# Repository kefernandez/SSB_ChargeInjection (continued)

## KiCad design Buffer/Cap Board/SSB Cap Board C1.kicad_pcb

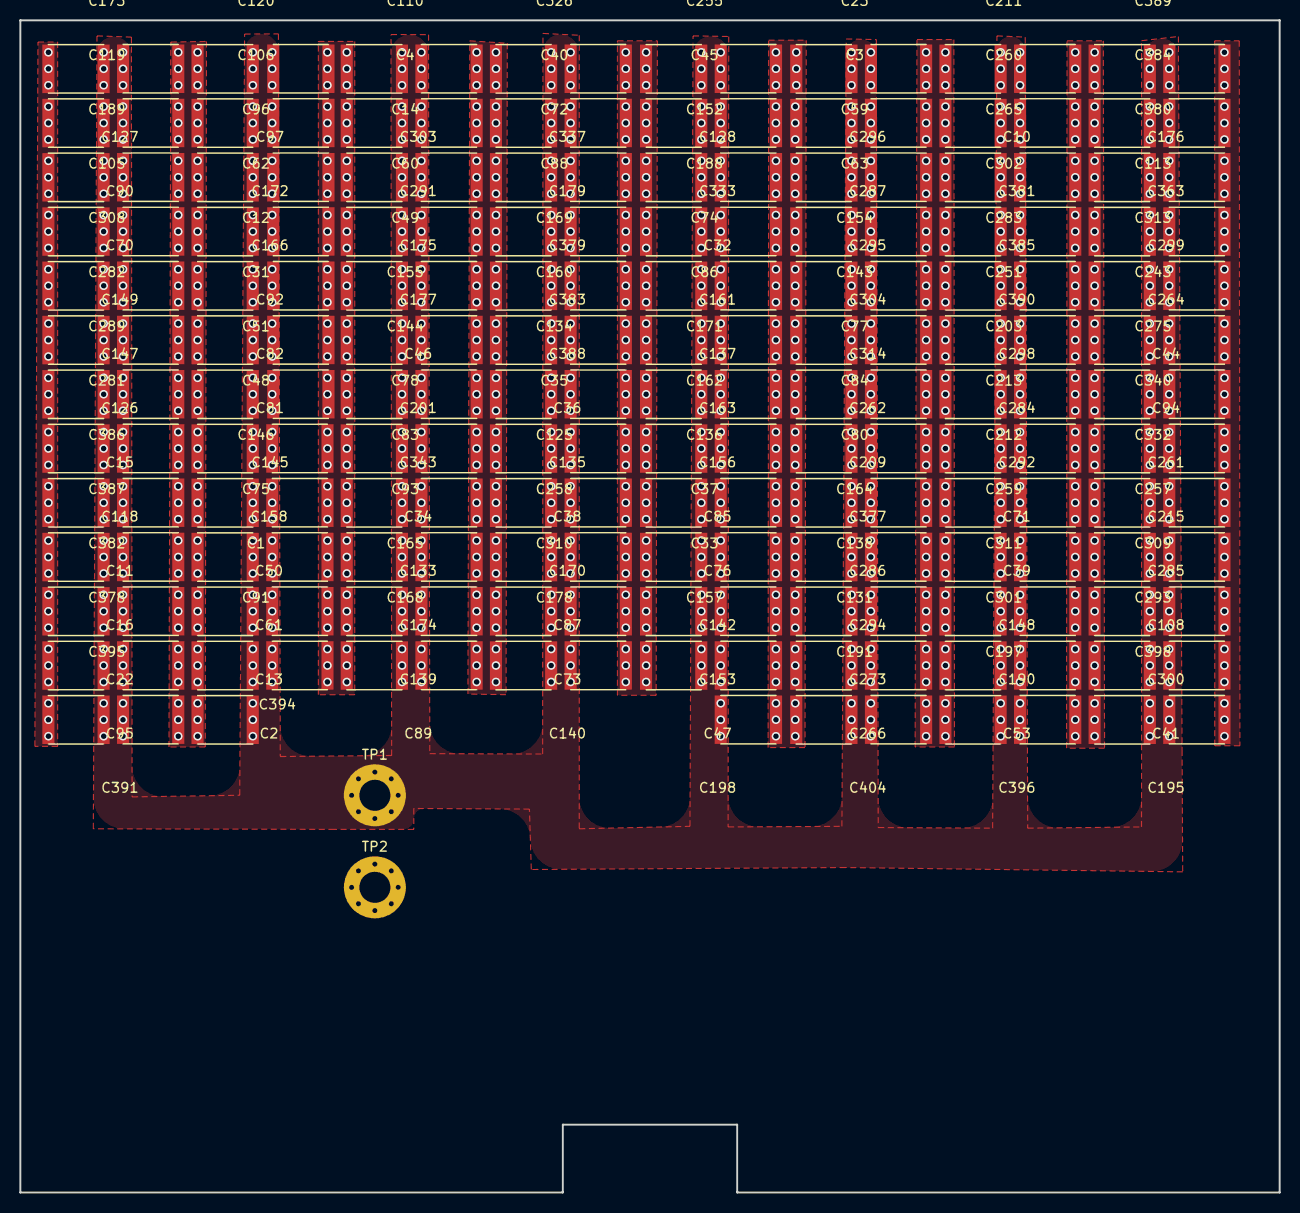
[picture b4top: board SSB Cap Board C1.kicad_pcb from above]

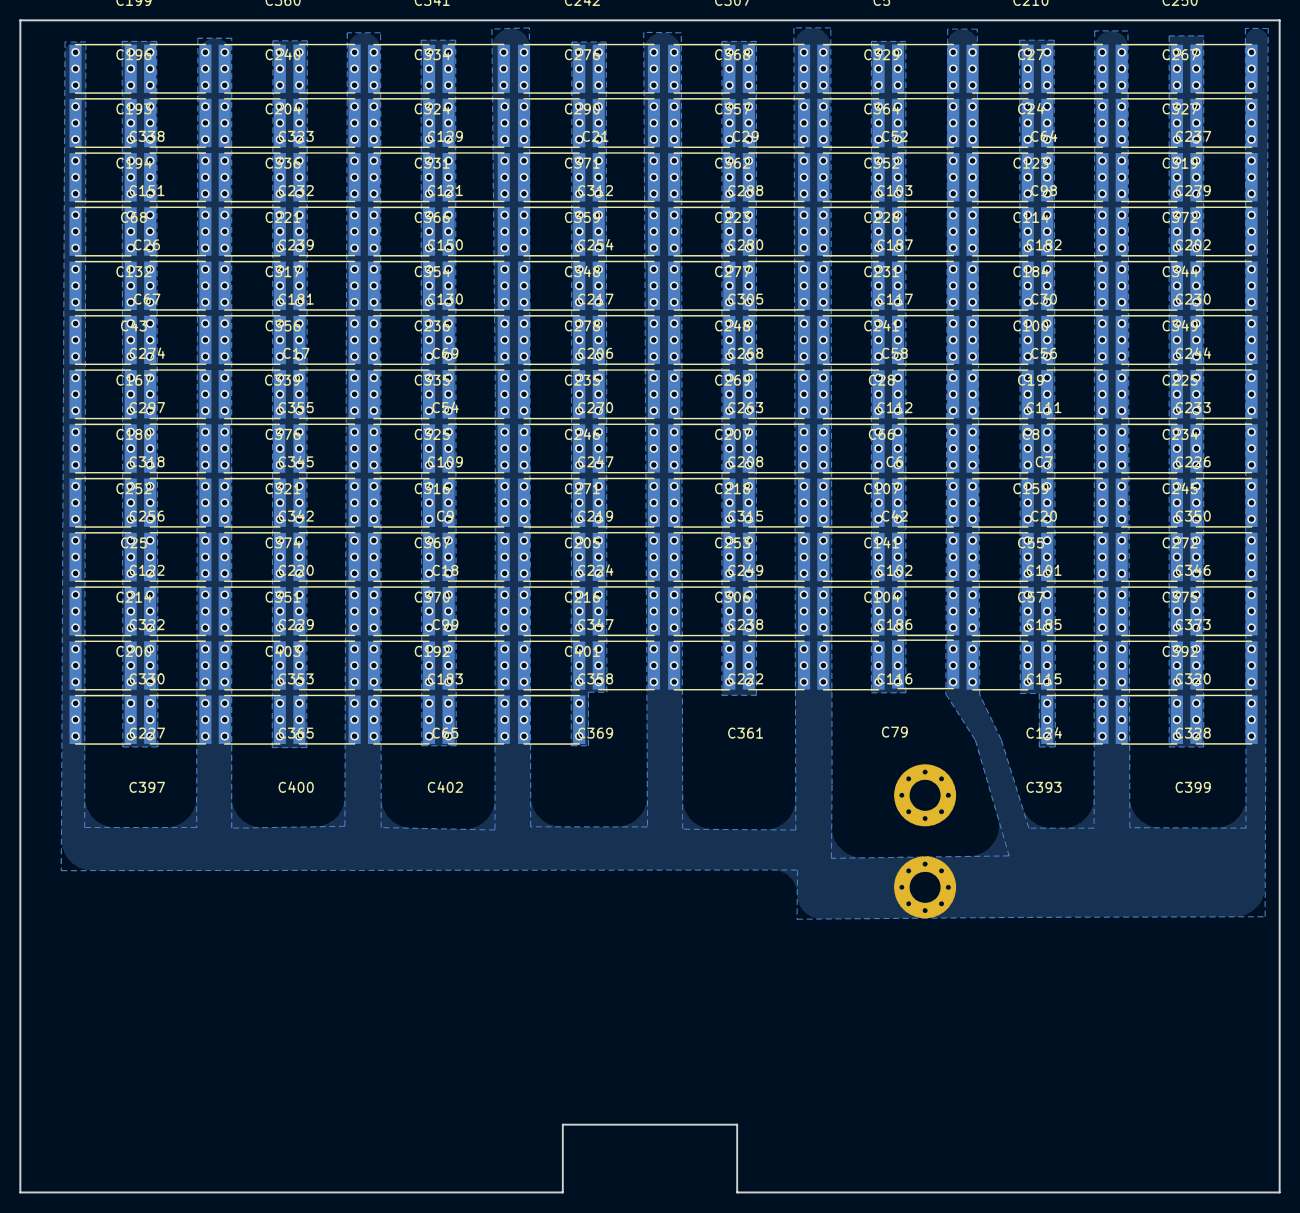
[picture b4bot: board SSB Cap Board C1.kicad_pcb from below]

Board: 2 copper layers, 130.0 x 121.0 mm, 406 parts (202 on the bottom side), 2 nets, no tracks yet.

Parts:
C1, C2, C3, C4, C5, C6, C7, C8, C9, C10, C11, C12, C13, C14, C15, C16, C17, C18, C19, C20, C21, C22, C23, C24, C25, C26, C27, C28, C29, C30, C31, C32, C33, C34, C35, C36, C37, C38, C39, C40, C41, C42, C43, C44, C45, C46, C47, C48, C49, C50, C51, C52, C53, C54, C55, C56, C57, C58, C59, C60, C61, C62, C63, C64, C65, C66, C67, C68, C69, C70, C71, C72, C73, C74, C75, C76, C77, C78, C79, C80, C81, C82, C83, C84, C85, C86, C87, C88, C89, C90, C91, C92, C93, C94, C95, C96, C97, C98, C99, C100, C101, C102, C103, C104, C105, C106, C107, C108, C109, C110, C111, C112, C113, C114, C115, C116, C117, C118, C119, C120, C121, C122, C123, C124, C125, C126, C127, C128, C129, C130, C131, C132, C133, C134, C135, C136, C137, C138, C139, C140, C141, C142, C143, C144, C145, C146, C147, C148, C149, C150, C151, C152, C153, C154, C155, C156, C157, C158, C159, C160, C161, C162, C163, C164, C165, C166, C167, C168, C169, C170, C171, C172, C173, C174, C175, C176, C177, C178, C179, C180, C181, C182, C183, C184, C185, C186, C187, C188, C189, C190, C191, C192, C193, C194, C195, C196, C197, C198, C199, C200, C201, C202, C203, C204, C205, C206, C207, C208, C209, C210, C211, C212, C213, C214, C215, C216, C217, C218, C219, C220, C221, C222, C223, C224, C225, C226, C227, C228, C229, C230, C231, C232, C233, C234, C235, C236, C237, C238, C239, C240, C241, C242, C243, C244, C245, C246, C247, C248, C249, C250, C251, C252, C253, C254, C255, C256, C257, C258, C259, C260, C261, C262, C263, C264, C265, C266, C267, C268, C269, C270, C271, C272, C273, C274, C275, C276, C277, C278, C279, C280, C281, C282, C283, C284, C285, C286, C287, C288, C289, C290, C291, C292, C293, C294, C295, C296, C297, C298, C299, C300, C301, C302, C303, C304, C305, C306, C307, C308, C309, C310, C311, C312, C313, C314, C315, C316, C317, C318, C319, C320, C321, C322, C323, C324, C325, C326, C327, C328, C329, C330, C331, C332, C333, C334, C335, C336, C337, C338, C339, C340, C341, C342, C343, C344, C345, C346, C347, C348, C349, C350, C351, C352, C353, C354, C355, C356, C357, C358, C359, C360, C361, C362, C363, C364, C365, C366, C367, C368, C369, C370, C371, C372, C373, C374, C375, C376, C377, C378, C379, C380, C381, C382, C383, C384, C385, C386, C387, C388, C389, C390, C391, C392, C393, C394, C395, C396, C397, C398, C399, C400, C401, C402, C403, C404: C; C_2220_Sm
TP1, TP2: TestPoint; MountingHole_3.2mm_M3_Pad_Via

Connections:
/C1+: C1.1, C2.1, C3.1, C4.1, C5.1, C6.1, C7.1, C8.1, C9.1, C10.1, C11.1, C12.1, C13.1, C14.1, C15.1, C16.1, C17.1, C18.1, C19.1, C20.1, C21.1, C22.1, C23.1, C24.1, C25.1, C26.1, C27.1, C28.1, C29.1, C30.1, C31.1, C32.1, C33.1, C34.1, C35.1, C36.1, C37.1, C38.1, C39.1, C40.1, C41.1, C42.1, C43.1, C44.1, C45.1, C46.1, C47.1, C48.1, C49.1, C50.1, C51.1, C52.1, C53.1, C54.1, C55.1, C56.1, C57.1, C58.1, C59.1, C60.1, C61.1, C62.1, C63.1, C64.1, C65.1, C66.1, C67.1, C68.1, C69.1, C70.1, C71.1, C72.1, C73.1, C74.1, C75.1, C76.1, C77.1, C78.1, C79.1, C80.1, C81.1, C82.1, C83.1, C84.1, C85.1, C86.1, C87.1, C88.1, C89.1, C90.1, C91.1, C92.1, C93.1, C94.1, C95.1, C96.1, C97.1, C98.1, C99.1, C100.1, C101.1, C102.1, C103.1, C104.1, C105.1, C106.1, C107.1, C108.1, C109.1, C110.1, C111.1, C112.1, C113.1, C114.1, C115.1, C116.1, C117.1, C118.1, C119.1, C120.1, C121.1, C122.1, C123.1, C124.1, C125.1, C126.1, C127.1, C128.1, C129.1, C130.1, C131.1, C132.1, C133.1, C134.1, C135.1, C136.1, C137.1, C138.1, C139.1, C140.1, C141.1, C142.1, C143.1, C144.1, C145.1, C146.1, C147.1, C148.1, C149.1, C150.1, C151.1, C152.1, C153.1, C154.1, C155.1, C156.1, C157.1, C158.1, C159.1, C160.1, C161.1, C162.1, C163.1, C164.1, C165.1, C166.1, C167.1, C168.1, C169.1, C170.1, C171.1, C172.1, C173.1, C174.1, C175.1, C176.1, C177.1, C178.1, C179.1, C180.1, C181.1, C182.1, C183.1, C184.1, C185.1, C186.1, C187.1, C188.1, C189.1, C190.1, C191.1, C192.1, C193.1, C194.1, C195.1, C196.1, C197.1, C198.1, C199.1, C200.1, C201.1, C202.1, C203.1, C204.1, C205.1, C206.1, C207.1, C208.1, C209.1, C210.1, C211.1, C212.1, C213.1, C214.1, C215.1, C216.1, C217.1, C218.1, C219.1, C220.1, C221.1, C222.1, C223.1, C224.1, C225.1, C226.1, C227.1, C228.1, C229.1, C230.1, C231.1, C232.1, C233.1, C234.1, C235.1, C236.1, C237.1, C238.1, C239.1, C240.1, C241.1, C242.1, C243.1, C244.1, C245.1, C246.1, C247.1, C248.1, C249.1, C250.1, C251.1, C252.1, C253.1, C254.1, C255.1, C256.1, C257.1, C258.1, C259.1, C260.1, C261.1, C262.1, C263.1, C264.1, C265.1, C266.1, C267.1, C268.1, C269.1, C270.1, C271.1, C272.1, C273.1, C274.1, C275.1, C276.1, C277.1, C278.1, C279.1, C280.1, C281.1, C282.1, C283.1, C284.1, C285.1, C286.1, C287.1, C288.1, C289.1, C290.1, C291.1, C292.1, C293.1, C294.1, C295.1, C296.1, C297.1, C298.1, C299.1, C300.1, C301.1, C302.1, C303.1, C304.1, C305.1, C306.1, C307.1, C308.1, C309.1, C310.1, C311.1, C312.1, C313.1, C314.1, C315.1, C316.1, C317.1, C318.1, C319.1, C320.1, C321.1, C322.1, C323.1, C324.1, C325.1, C326.1, C327.1, C328.1, C329.1, C330.1, C331.1, C332.1, C333.1, C334.1, C335.1, C336.1, C337.1, C338.1, C339.1, C340.1, C341.1, C342.1, C343.1, C344.1, C345.1, C346.1, C347.1, C348.1, C349.1, C350.1, C351.1, C352.1, C353.1, C354.1, C355.1, C356.1, C357.1, C358.1, C359.1, C360.1, C361.1, C362.1, C363.1, C364.1, C365.1, C366.1, C367.1, C368.1, C369.1, C370.1, C371.1, C372.1, C373.1, C374.1, C375.1, C376.1, C377.1, C378.1, C379.1, C380.1, C381.1, C382.1, C383.1, C384.1, C385.1, C386.1, C387.1, C388.1, C389.1, C390.1, C391.1, C392.1, C393.1, C394.1, C395.1, C396.1, C397.1, C398.1, C399.1, C400.1, C401.1, C402.1, C403.1, C404.1, TP1.1
/C1-: C1.2, C2.2, C3.2, C4.2, C5.2, C6.2, C7.2, C8.2, C9.2, C10.2, C11.2, C12.2, C13.2, C14.2, C15.2, C16.2, C17.2, C18.2, C19.2, C20.2, C21.2, C22.2, C23.2, C24.2, C25.2, C26.2, C27.2, C28.2, C29.2, C30.2, C31.2, C32.2, C33.2, C34.2, C35.2, C36.2, C37.2, C38.2, C39.2, C40.2, C41.2, C42.2, C43.2, C44.2, C45.2, C46.2, C47.2, C48.2, C49.2, C50.2, C51.2, C52.2, C53.2, C54.2, C55.2, C56.2, C57.2, C58.2, C59.2, C60.2, C61.2, C62.2, C63.2, C64.2, C65.2, C66.2, C67.2, C68.2, C69.2, C70.2, C71.2, C72.2, C73.2, C74.2, C75.2, C76.2, C77.2, C78.2, C79.2, C80.2, C81.2, C82.2, C83.2, C84.2, C85.2, C86.2, C87.2, C88.2, C89.2, C90.2, C91.2, C92.2, C93.2, C94.2, C95.2, C96.2, C97.2, C98.2, C99.2, C100.2, C101.2, C102.2, C103.2, C104.2, C105.2, C106.2, C107.2, C108.2, C109.2, C110.2, C111.2, C112.2, C113.2, C114.2, C115.2, C116.2, C117.2, C118.2, C119.2, C120.2, C121.2, C122.2, C123.2, C124.2, C125.2, C126.2, C127.2, C128.2, C129.2, C130.2, C131.2, C132.2, C133.2, C134.2, C135.2, C136.2, C137.2, C138.2, C139.2, C140.2, C141.2, C142.2, C143.2, C144.2, C145.2, C146.2, C147.2, C148.2, C149.2, C150.2, C151.2, C152.2, C153.2, C154.2, C155.2, C156.2, C157.2, C158.2, C159.2, C160.2, C161.2, C162.2, C163.2, C164.2, C165.2, C166.2, C167.2, C168.2, C169.2, C170.2, C171.2, C172.2, C173.2, C174.2, C175.2, C176.2, C177.2, C178.2, C179.2, C180.2, C181.2, C182.2, C183.2, C184.2, C185.2, C186.2, C187.2, C188.2, C189.2, C190.2, C191.2, C192.2, C193.2, C194.2, C195.2, C196.2, C197.2, C198.2, C199.2, C200.2, C201.2, C202.2, C203.2, C204.2, C205.2, C206.2, C207.2, C208.2, C209.2, C210.2, C211.2, C212.2, C213.2, C214.2, C215.2, C216.2, C217.2, C218.2, C219.2, C220.2, C221.2, C222.2, C223.2, C224.2, C225.2, C226.2, C227.2, C228.2, C229.2, C230.2, C231.2, C232.2, C233.2, C234.2, C235.2, C236.2, C237.2, C238.2, C239.2, C240.2, C241.2, C242.2, C243.2, C244.2, C245.2, C246.2, C247.2, C248.2, C249.2, C250.2, C251.2, C252.2, C253.2, C254.2, C255.2, C256.2, C257.2, C258.2, C259.2, C260.2, C261.2, C262.2, C263.2, C264.2, C265.2, C266.2, C267.2, C268.2, C269.2, C270.2, C271.2, C272.2, C273.2, C274.2, C275.2, C276.2, C277.2, C278.2, C279.2, C280.2, C281.2, C282.2, C283.2, C284.2, C285.2, C286.2, C287.2, C288.2, C289.2, C290.2, C291.2, C292.2, C293.2, C294.2, C295.2, C296.2, C297.2, C298.2, C299.2, C300.2, C301.2, C302.2, C303.2, C304.2, C305.2, C306.2, C307.2, C308.2, C309.2, C310.2, C311.2, C312.2, C313.2, C314.2, C315.2, C316.2, C317.2, C318.2, C319.2, C320.2, C321.2, C322.2, C323.2, C324.2, C325.2, C326.2, C327.2, C328.2, C329.2, C330.2, C331.2, C332.2, C333.2, C334.2, C335.2, C336.2, C337.2, C338.2, C339.2, C340.2, C341.2, C342.2, C343.2, C344.2, C345.2, C346.2, C347.2, C348.2, C349.2, C350.2, C351.2, C352.2, C353.2, C354.2, C355.2, C356.2, C357.2, C358.2, C359.2, C360.2, C361.2, C362.2, C363.2, C364.2, C365.2, C366.2, C367.2, C368.2, C369.2, C370.2, C371.2, C372.2, C373.2, C374.2, C375.2, C376.2, C377.2, C378.2, C379.2, C380.2, C381.2, C382.2, C383.2, C384.2, C385.2, C386.2, C387.2, C388.2, C389.2, C390.2, C391.2, C392.2, C393.2, C394.2, C395.2, C396.2, C397.2, C398.2, C399.2, C400.2, C401.2, C402.2, C403.2, C404.2, TP2.1

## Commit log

2021-04-21 Uploaded all charge injection documents
    Placed all of my local charge injection documents into the git repo
2021-05-25 Updated schematic
    Updated schematic/layout with resistor and cap values
2021-07-21 Data from lab
    Uploading scope images from the data collected in lab
2022-12-01 updated pcb and test results and graphics
    All relevant files up to charge injection journal
2022-12-01 Simulations
    Added simulation files from harddrive
2022-12-01 Graphics, code
    adding updated code and graphics
